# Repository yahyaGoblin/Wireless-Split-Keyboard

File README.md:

# Wireless Split Keyboard

A fully wireless split keyboard PCB, designed for ergonomic typing with no cables between halves or to the host.

## Features

- Wireless split design — no cable between halves
- Bluetooth LE connectivity to host
- Battery powered on each half
- 1N4148 diodes for full anti-ghosting / n-key rollover
- Low power design for extended battery life

## Bill of Materials

| Ref | Component | Value / Model | Qty |
|-----|-----------|---------------|-----|
| U1–U2 | Wireless MCU | nice!nano (nRF52840) | 2 |
| SW1–SWn | Mechanical Key Switch | Cherry MX compatible | n |
| D1–Dn | Switching Diode | 1N4148 SOD-123 | n |
| BAT1–BAT2 | LiPo Battery | 3.7V 301230 or similar | 2 |
| C1–C2 | Decoupling Capacitor | 100nF 0402 | 2 |
| R1–R2 | Pull-up Resistor | 4.7kΩ 0402 | 2 |
| SW_RESET1–2 | Reset Button | 3x6mm tactile switch | 2 |
| SW_POWER1–2 | Power Switch | MSK-12C02 slide switch | 2 |
| J1–J2 | Battery Connector | JST PH 2.0 2-pin | 2 |

> Update switch quantities (n) based on your layout. Part numbers are suggestions.

## PCB Design

Each half is an independent PCB with its own MCU and battery:
- **Left half** — acts as the central device, connects to the host via Bluetooth
- **Right half** — acts as a peripheral, communicates wirelessly to the left half

## Fabrication

Gerber files for both halves are in the `/gerbers` folder.

Recommended specs:
- Layers: 2
- Thickness: 1.6mm
- Surface finish: HASL or ENIG

## Firmware

Designed for [ZMK Firmware](https://zmk.dev/), which has first-class support for wireless split keyboards and the nice!nano.

## Battery Life

Estimated battery life varies by usage and battery capacity. With a 110mAh battery expect several weeks of typical use.

## Project Files

| File | Description |
|------|-------------|
| `keyboard_left.kicad_sch` | Left half schematic |
| `keyboard_right.kicad_sch` | Right half schematic |
| `keyboard_left.kicad_pcb` | Left half PCB layout |
| `keyboard_right.kicad_pcb` | Right half PCB layout |
| `/gerbers` | Fabrication files for both halves |

## License

Open source hardware — feel free to modify and build your own.

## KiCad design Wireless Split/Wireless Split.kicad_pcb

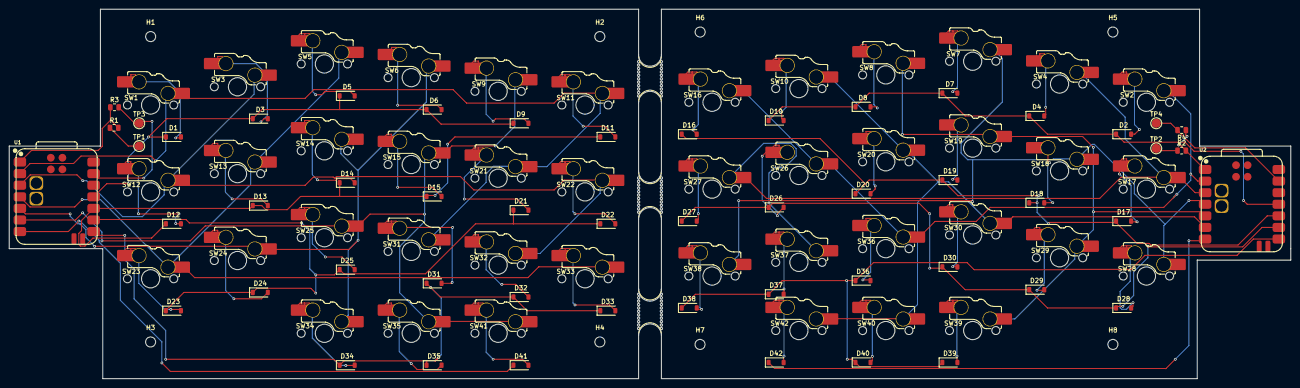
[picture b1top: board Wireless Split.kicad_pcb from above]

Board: 2 copper layers, 281.0 x 81.0 mm, 105 parts (0 on the bottom side), 67 nets.

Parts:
BO1, BO2, BO3: Break off; mouse-bite-5mm-slot
D1, D2, D3, D4, D5, D6, D7, D8, D9, D10, D11, D12, D13, D14, D15, D16, D17, D18, D19, D20, D21, D22, D23, D24, D25, D26, D27, D28, D29, D30, D31, D32, D33, D34, D35, D36, D37, D38, D39, D40, D41, D42: D; D_SOD-123
H1, H2, H3, H4, H5, H6, H7, H8: MountingHole; MountingHole_2.2mm_M2
R1, R2: 806K; R_0805_2012Metric
R3, R4: 2M; R_0805_2012Metric
SW1, SW2, SW3, SW4, SW5, SW6, SW7, SW8, SW9, SW10, SW11, SW12, SW13, SW14, SW15, SW16, SW17, SW18, SW19, SW20, SW21, SW22, SW23, SW24, SW25, SW26, SW27, SW28, SW29, SW30, SW31, SW32, SW33, SW34, SW35, SW36, SW37, SW38, SW39, SW40, SW41, SW42: SW_Push; SW_MX_HS_KS-2P02B01-01_1u
TP1, TP2, TP3, TP4: TestPoint; TestPoint_Pad_D2.0mm
U1, U2: XIAO-nRF52840-SMD; modified-XIAO-nRF52840-SMD

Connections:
/Left/BT_PIN: R1.2, R3.1, U1.1 (P0.02_A0_D0)
/Left/COL0: SW1.1, SW11.1, SW21.1, SW31.1, U1.2 (P0.03_A1_D1)
/Left/COL1: SW3.1, SW12.1, SW22.1, SW32.1, U1.3 (P0.28_A2_D2)
/Left/COL2: SW5.1, SW13.1, SW23.1, SW33.1, U1.4 (P0.29_A3_D3)
/Left/COL3: SW6.1, SW14.1, SW24.1, SW34.1, U1.5 (P0.04_A4_D4_SDA)
/Left/COL4: SW9.1, SW15.1, SW25.1, SW35.1, SW41.1, U1.6 (P0.05_A5_D5_SCL)
/Left/ROW0: D1.1 (K), D3.1 (K), D5.1 (K), D6.1 (K), D9.1 (K), U1.11 (P1.15_D10_MOSI)
/Left/ROW1: D11.1 (K), D12.1 (K), D13.1 (K), D14.1 (K), D15.1 (K), U1.10 (P1.14_D9_MISO)
/Left/ROW2: D21.1 (K), D22.1 (K), D23.1 (K), D24.1 (K), D25.1 (K), U1.9 (P1.13_D8_SCK)
/Left/ROW3: D31.1 (K), D32.1 (K), D33.1 (K), D34.1 (K), D35.1 (K), U1.8 (P1.12_D7_RX)
/Left/ROW4: D41.1 (K), U1.7 (P1.11_D6_TX)
/Left/VBAT: R1.1, TP1.1 (1_1)
/Right/BT_PIN: R2.2, R4.1, U2.1 (P0.02_A0_D0)
/Right/COL0: SW2.1, SW16.1, SW26.1, SW36.1, U2.2 (P0.03_A1_D1)
/Right/COL1: SW4.1, SW17.1, SW27.1, SW37.1, U2.3 (P0.28_A2_D2)
/Right/COL2: SW7.1, SW18.1, SW28.1, SW38.1, U2.4 (P0.29_A3_D3)
/Right/COL3: SW8.1, SW19.1, SW29.1, SW39.1, U2.5 (P0.04_A4_D4_SDA)
/Right/COL4: SW10.1, SW20.1, SW30.1, SW40.1, SW42.1, U2.6 (P0.05_A5_D5_SCL)
/Right/ROW0: D2.1 (K), D4.1 (K), D7.1 (K), D8.1 (K), D10.1 (K), U2.11 (P1.15_D10_MOSI)
/Right/ROW1: D16.1 (K), D17.1 (K), D18.1 (K), D19.1 (K), D20.1 (K), U2.10 (P1.14_D9_MISO)
/Right/ROW2: D26.1 (K), D27.1 (K), D28.1 (K), D29.1 (K), D30.1 (K), U2.9 (P1.13_D8_SCK)
/Right/ROW3: D36.1 (K), D37.1 (K), D38.1 (K), D39.1 (K), D40.1 (K), U2.8 (P1.12_D7_RX)
/Right/ROW4: D42.1 (K), U2.7 (P1.11_D6_TX)
/Right/VBAT: R2.1, TP2.1 (1_1)
GND: R3.2, R4.2, TP3.1 (1_1), TP4.1 (1_1), U1.13 (GND), U2.13 (GND)
unnamed: D1.2 (A), SW1.2
unnamed: D2.2 (A), SW2.2
unnamed: D3.2 (A), SW3.2
unnamed: D4.2 (A), SW4.2
unnamed: D5.2 (A), SW5.2
unnamed: D6.2 (A), SW6.2
unnamed: D7.2 (A), SW7.2
unnamed: D8.2 (A), SW8.2
unnamed: D9.2 (A), SW9.2
unnamed: D10.2 (A), SW10.2
unnamed: D11.2 (A), SW11.2
unnamed: D12.2 (A), SW12.2
unnamed: D13.2 (A), SW13.2
unnamed: D14.2 (A), SW14.2
unnamed: D15.2 (A), SW15.2
unnamed: D16.2 (A), SW16.2
unnamed: D17.2 (A), SW17.2
unnamed: D18.2 (A), SW18.2
unnamed: D19.2 (A), SW19.2
unnamed: D20.2 (A), SW20.2
unnamed: D21.2 (A), SW21.2
unnamed: D22.2 (A), SW22.2
unnamed: D23.2 (A), SW23.2
unnamed: D24.2 (A), SW24.2
unnamed: D25.2 (A), SW25.2
unnamed: D26.2 (A), SW26.2
unnamed: D27.2 (A), SW27.2
unnamed: D28.2 (A), SW28.2
unnamed: D29.2 (A), SW29.2
unnamed: D30.2 (A), SW30.2
unnamed: D31.2 (A), SW31.2
unnamed: D32.2 (A), SW32.2
unnamed: D33.2 (A), SW33.2
unnamed: D34.2 (A), SW34.2
unnamed: D35.2 (A), SW35.2
unnamed: D36.2 (A), SW36.2
unnamed: D37.2 (A), SW37.2
unnamed: D38.2 (A), SW38.2
unnamed: D39.2 (A), SW39.2
unnamed: D40.2 (A), SW40.2
unnamed: D41.2 (A), SW41.2
unnamed: D42.2 (A), SW42.2

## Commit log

2026-05-29 final
